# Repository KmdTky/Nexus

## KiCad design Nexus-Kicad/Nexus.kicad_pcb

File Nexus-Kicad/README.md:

# Nexus
RaspberryPi4で3線のシリアルサーボ(Feetech社STS3215を想定)を使用するためのHAT
今後,近藤科学社KRS4014,34,6003HVに変更予定

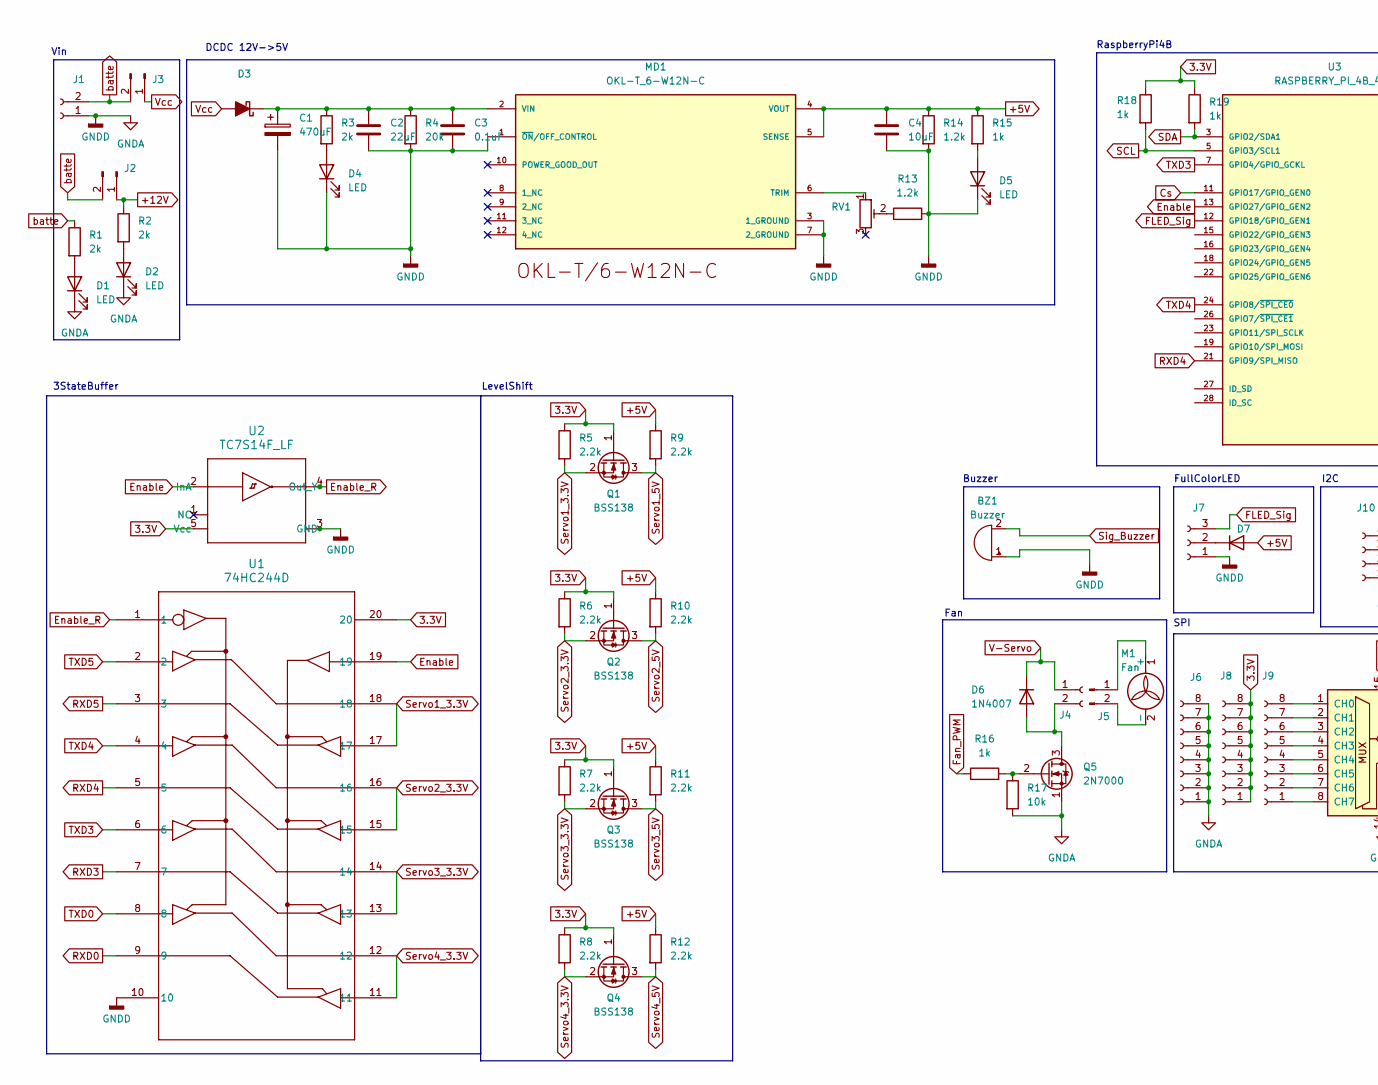
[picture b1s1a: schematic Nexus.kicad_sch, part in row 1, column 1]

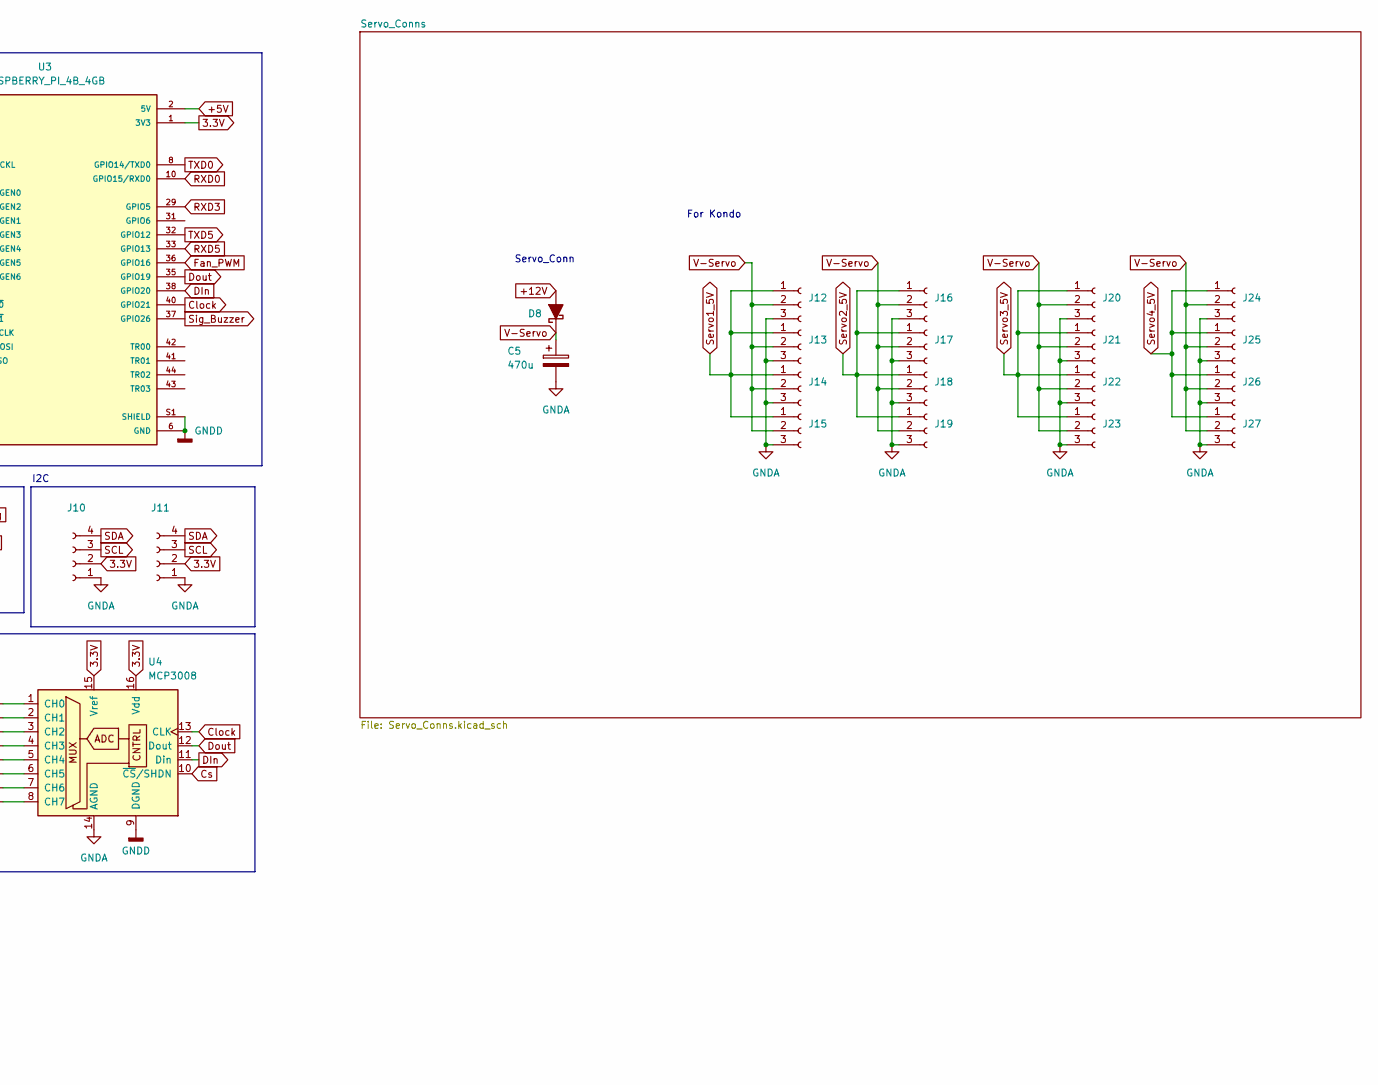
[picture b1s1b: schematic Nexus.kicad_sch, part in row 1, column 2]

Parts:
BZ1: Buzzer; Buzzer_15x7.5RM7.6
C1: 470uF; CP_Radial_D10.0mm_P5.00mm
C2: 22uF; C_0603_1608Metric
C3: 0.1uF; C_0603_1608Metric
C4: 10uF; C_0603_1608Metric
C5: 470u; CP_Radial_D10.0mm_P5.00mm
D1, D2, D4, D5: LED; LED_0603_1608Metric
D3: D_Schottky_Filled; D_DO-201AE_P12.70mm_Horizontal
D6: 1N4007; D_DO-41_SOD81_P7.62mm_Horizontal
D7: D; D_DO-34_SOD68_P7.62mm_Horizontal
D8: D_Schottky_Filled; D_DO-201AD_P12.70mm_Horizontal
J1: Conn_01x02_Socket; AMASS_XT30U-F_1x02_P5.0mm_Vertical
J2, J3: Conn_01x02_Pin; AMASS_XT30U-F_1x02_P5.0mm_Vertical
J4: Conn_01x02_Socket; PinSocket_1x02_P2.54mm_Vertical
J5: Conn_01x02_Pin
J6, J8, J9: Conn_01x08_Socket; PinSocket_1x08_P2.54mm_Vertical
J7: Conn_01x03_Socket; PinSocket_1x03_P2.54mm_Vertical
J10, J11: Conn_01x04_Socket; PinSocket_1x04_P2.54mm_Vertical
J12, J13, J14, J15, J16, J17, J18, J19, J20, J21, J22, J23, J24, J25, J26, J27: Conn_01x03_Socket; PinHeader_1x03_P2.54mm_Vertical
M1: Fan
MD1: OKL-T_6-W12N-C; MURATA_OKL-T-6-W12N-C_0; MOUSER_PART_NUMBER 580-OKL-T/6-W12N-C; MOUSER_DESCRIPTION Non-Isolated DC/DC Converters 12Vin .59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
Q1, Q2, Q3, Q4: BSS138; SOT-23
Q5: 2N7000; TO-92_Inline
R1, R2, R3: 2k; R_0603_1608Metric
R4: 20k; R_0603_1608Metric
R5, R6, R7, R8, R9, R10, R11, R12: 2.2k; R_0603_1608Metric
R13, R14: 1.2k; R_0603_1608Metric
R15, R16, R18, R19: 1k; R_0603_1608Metric
R17: 10k; R_0603_1608Metric
RV1: R_Potentiometer_Trim; Potentiometer_Runtron_RM-065_Vertical
U1: 74HC244D; SOIC20_TOS
U2: TC7S14F_LF; SOT-25 SMV_TOS
U3: RASPBERRY_PI_4B_4GB; MODULE_RASPBERRY_PI_4B_4GB; PARTREV 4
U4: MCP3008; DIP-16_W7.62mm_Socket

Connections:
3.3V: J8.1, J8.2, J8.3, J8.4, J8.5, J8.6, J8.7, J8.8, J10.2, J11.2, Q1.1 (G), Q2.1 (G), Q3.1 (G), Q4.1 (G), R5.1, R6.1, R7.1, R8.1, R18.1, R19.1, U1.20, U2.5 (Vcc), U3.1 (3V3), U3.17 (3V3), U4.15 (Vref), U4.16 (Vdd)
+5V: C4.1, D7.2 (A), MD1.4 (VOUT), MD1.5 (SENSE), R9.1, R10.1, R11.1, R12.1, R14.1, R15.1, U3.2 (5V), U3.4 (5V)
+12V: D8.2 (A), J2.1, R2.1
Clock: U3.40 (GPIO21), U4.13 (CLK)
Cs: U3.11 (GPIO17/GPIO_GEN0), U4.10 (~CS/SHDN)
DIn: U3.38 (GPIO20), U4.11 (Din)
Dout: U3.35 (GPIO19), U4.12 (Dout)
Enable: U1.19, U2.2 (InA), U3.13 (GPIO27/GPIO_GEN2)
Enable_R: U1.1, U2.4 (Out_Y)
FLED_Sig: J7.3, U3.12 (GPIO18/GPIO_GEN1)
Fan_PWM: R16.1, U3.36 (GPIO16)
GNDA: BZ1.1 (+), C1.2, C2.2, C3.2, C4.2, C5.2, D1.1 (K), D2.1 (K), D4.1 (K), D5.1 (K), J1.1, J6.1, J6.2, J6.3, J6.4, J6.5, J6.6, J6.7, J6.8, J7.1, J10.1, J11.1, J12.3, J13.3, J14.3, J15.3, J16.3, J17.3, J18.3, J19.3, J20.3, J21.3, J22.3, J23.3, J24.3, J25.3, J26.3, J27.3, MD1.1 (~ON/OFF_CONTROL), MD1.3 (1_GROUND), MD1.7 (2_GROUND), Q5.1 (S), R4.2, R13.2, R14.2, R17.2, U1.10, U2.3 (GND), U3.6 (GND), U3.9 (GND), U3.14 (GND), U3.20 (GND), U3.25 (GND), U3.30 (GND), U3.34 (GND), U3.39 (GND), U3.S1 (SHIELD), U3.S2 (SHIELD), U3.S3 (SHIELD), U3.S4 (SHIELD), U4.9 (DGND), U4.14 (AGND)
unnamed: D1.2 (A), R1.2
unnamed: D2.2 (A), R2.2
unnamed: C1.1, C2.1, C3.1, D3.1 (K), MD1.2 (VIN), R3.1, R4.1
unnamed: D4.2 (A), R3.2
unnamed: D5.2 (A), R15.2
unnamed: D6.2 (A), J4.2, Q5.3 (D)
unnamed: D7.1 (K), J7.2
unnamed: J5.1, M1.1 (+)
unnamed: J5.2, M1.2 (-)
unnamed: J9.1, U4.8 (CH7)
unnamed: J9.2, U4.7 (CH6)
unnamed: J9.3, U4.6 (CH5)
unnamed: J9.4, U4.5 (CH4)
unnamed: J9.5, U4.4 (CH3)
unnamed: J9.6, U4.3 (CH2)
unnamed: J9.7, U4.2 (CH1)
unnamed: J9.8, U4.1 (CH0)
unnamed: MD1.6 (TRIM), RV1.1
unnamed: Q5.2 (G), R16.2, R17.1
unnamed: R13.1, RV1.2
RXD0: U1.9, U3.10 (GPIO15/RXD0)
RXD3: U1.7, U3.29 (GPIO5)
RXD4: U1.5, U3.21 (GPIO9/SPI_MISO)
RXD5: U1.3, U3.33 (GPIO13)
SCL: J10.3, J11.3, R18.2, U3.5 (GPIO3/SCL1)
SDA: J10.4, J11.4, R19.2, U3.3 (GPIO2/SDA1)
Servo1_3.3V: Q1.2 (S), R5.2, U1.17, U1.18
Servo1_5V: J12.1, J13.1, J14.1, J15.1, Q1.3 (D), R9.2
Servo2_3.3V: Q2.2 (S), R6.2, U1.15, U1.16
Servo2_5V: J16.1, J17.1, J18.1, J19.1, Q2.3 (D), R10.2
Servo3_3.3V: Q3.2 (S), R7.2, U1.13, U1.14
Servo3_5V: J20.1, J21.1, J22.1, J23.1, Q3.3 (D), R11.2
Servo4_3.3V: Q4.2 (S), R8.2, U1.11, U1.12
Servo4_5V: J24.1, J25.1, J26.1, J27.1, Q4.3 (D), R12.2
Sig_Buzzer: BZ1.2 (-), U3.37 (GPIO26)
TXD0: U1.8, U3.8 (GPIO14/TXD0)
TXD3: U1.6, U3.7 (GPIO4/GPIO_GCKL)
TXD4: U1.4, U3.24 (GPIO8/~SPI_CE0)
TXD5: U1.2, U3.32 (GPIO12)
V-Servo: C5.1, D6.1 (K), D8.1 (K), J4.1, J12.2, J13.2, J14.2, J15.2, J16.2, J17.2, J18.2, J19.2, J20.2, J21.2, J22.2, J23.2, J24.2, J25.2, J26.2, J27.2
Vcc: D3.2 (A), J3.1
batte: J1.2, J2.2, J3.2, R1.1

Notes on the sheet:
DCDC 12V->5V
SPI
3StateBuffer
LevelShift
Vin
Servo_Conn
RaspberryPi4B
I2C
For Kondo
Fan
FullColorLED
Buzzer

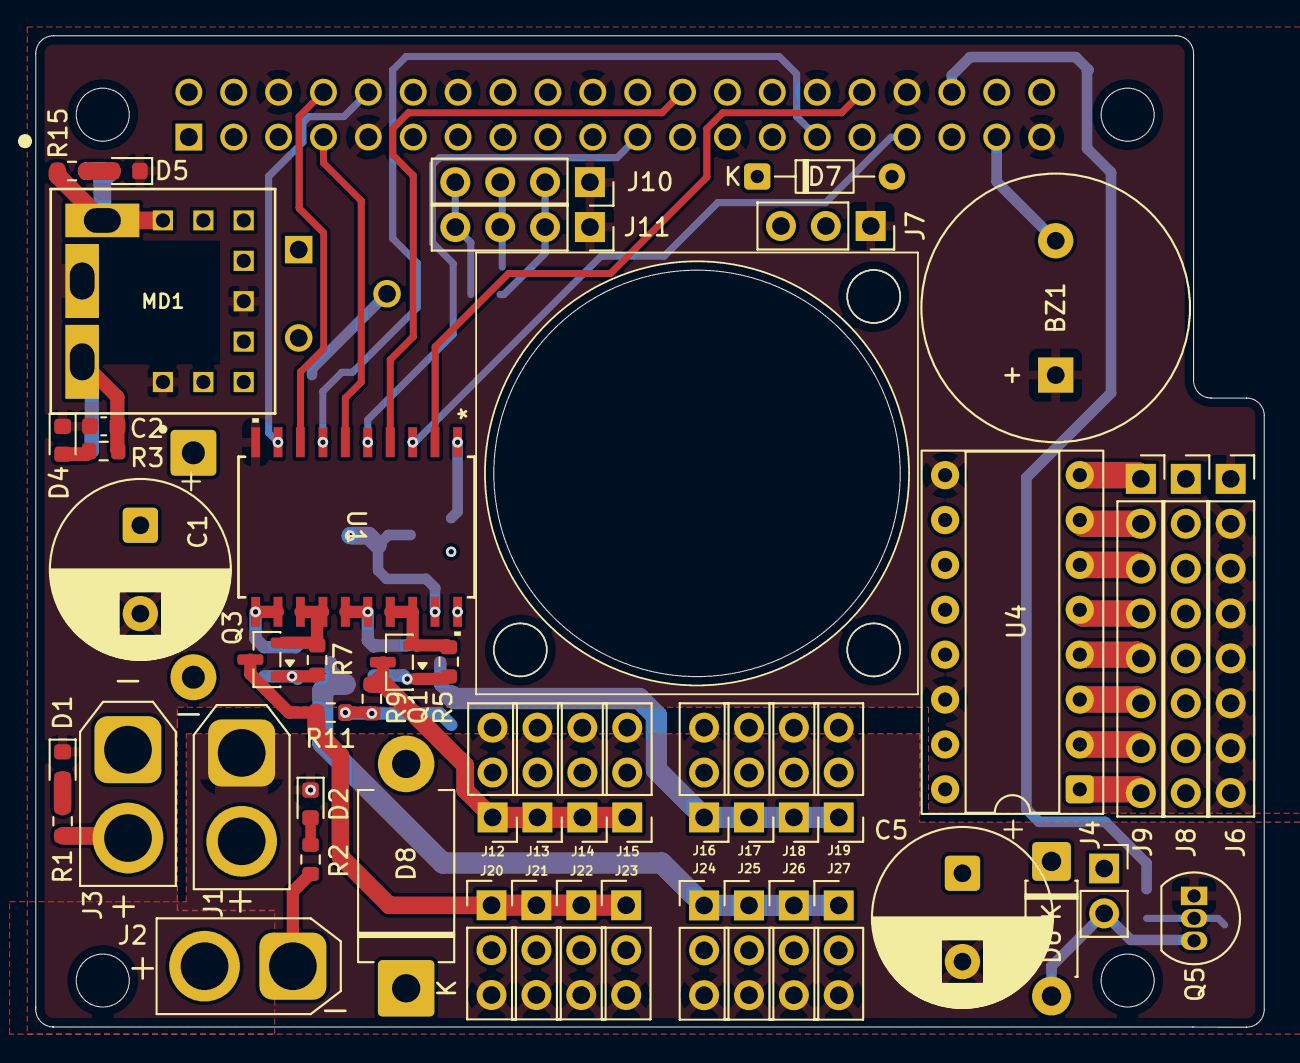
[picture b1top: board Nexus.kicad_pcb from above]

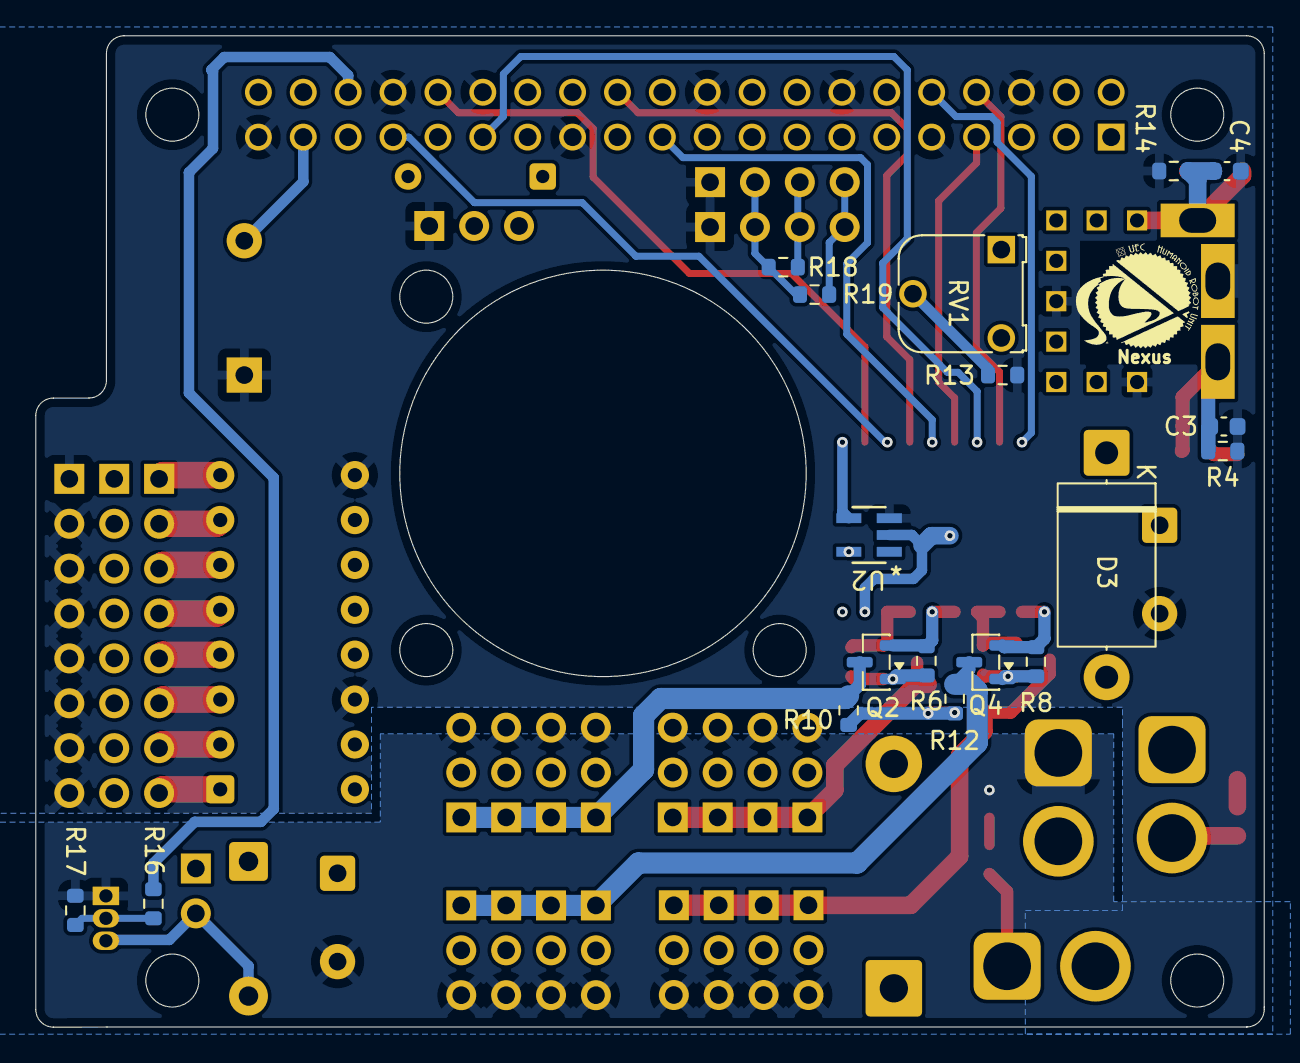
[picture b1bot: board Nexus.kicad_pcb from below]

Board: 6 copper layers, 69.5 x 56.1 mm, 70 parts (18 on the bottom side), 52 nets.

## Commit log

2026-03-15 Nexus
2026-03-15 Change Directry Name
2026-03-15 EDA ver 1.0
2026-03-15 add Right
2026-03-15 add PCB
2026-03-16 JLCPCB
2026-03-18 ver2
2026-03-19 add 3dbody
2026-03-19 change 3Dbody
2026-03-20 add stl model

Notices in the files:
Nexus-Kicad/Nexus.kicad_sch:
CC BY-NC-SA
